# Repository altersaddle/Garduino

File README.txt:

The purpose of this project is to enable data collection and eventually action to keep
plants alive in a garden.

This project encompasses five components:

1) The "Garduino" device itself, which manages the sensors and external controls

2) The Arduino software that's running on the device

3) A serial monitor that accepts serial (via bluetooth) data from the Garduino

4) A database to keep all of the data

5) A reporting application / system to let users manage the data

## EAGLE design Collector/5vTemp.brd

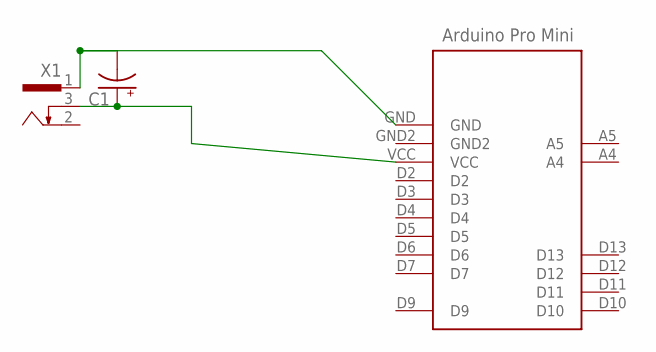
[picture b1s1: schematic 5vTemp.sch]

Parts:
C1: CPOL-USSANYO_C; SANYO-OSCON_C
U$1: ARDUINO_PRO_MINI_5V_V2V2; ARDUINO_PRO_MINI_5V_V2
X1: 733980-62

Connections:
unnamed: C1.+, U$1.VCC, X1.3
unnamed: C1.-, U$1.GND, X1.1

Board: 2 copper layers, 3 parts (0 on the bottom side), 2 nets, no tracks yet.

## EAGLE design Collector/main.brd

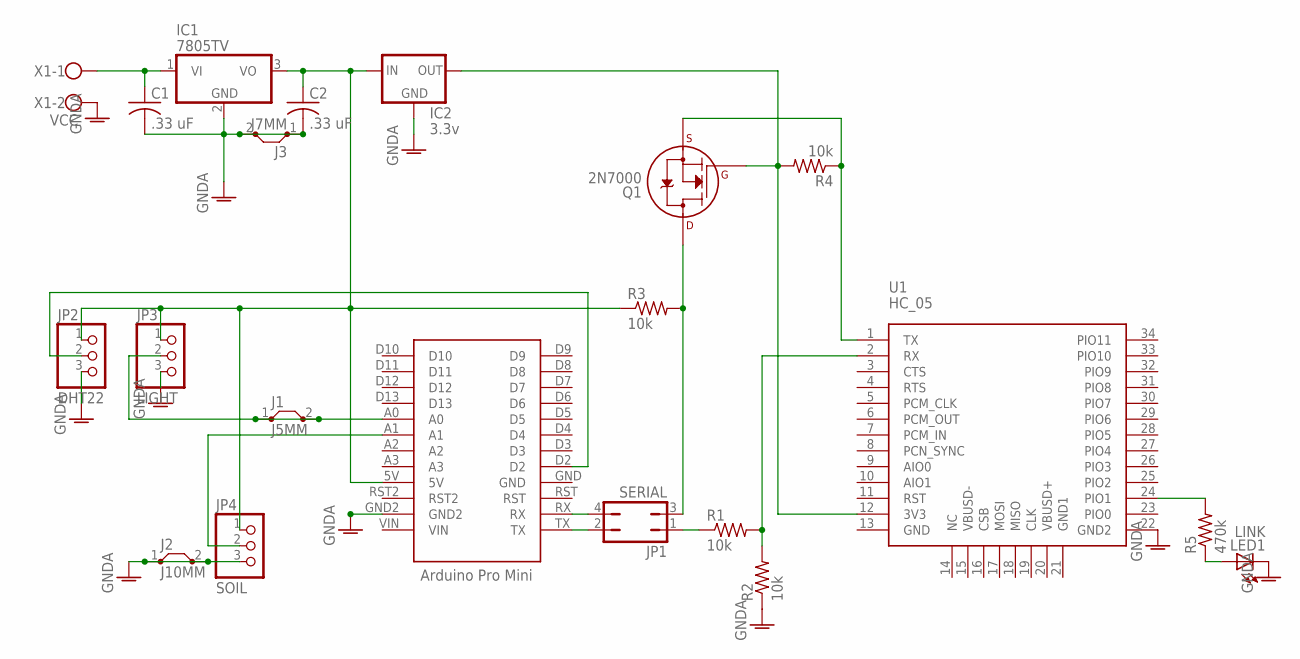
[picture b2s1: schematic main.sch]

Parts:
C1, C2: .33 uF; C025-050X050
IC1: 7805TV; TO220V
IC2: 3.3v; TO92-INLINE
J1: J5MM; 05
J2: J10MM; 10
J3: J7MM; 07
JP1: SERIAL; JP2Q
JP2: DHT22; 1X03
JP3: LIGHT; 1X03
JP4: SOIL; 1X03
LED1: LINK; LED3MM
Q1: 2N7000; TO-92
R1, R2, R3, R4: 10k; 0204/7
R5: 470k; 0204/7
U1: HC_05; BLUETOOTH_SMD
U$1: ARDUINO_PRO_MINI_5V_V1V1; ARDUINO_PRO_MINI_5V_V1
X1: VCC; W237-102

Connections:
GNDA: C1.2, C2.2, IC1.2 (GND), IC2.1 (GND), J2.1, J2.2, J3.1, J3.2, JP2.3, JP3.3, JP4.3, LED1.K (C), R2.1, U1.22 (GND2), U$1.GND2, X1.2
unnamed: IC2.3 (OUT), Q1.2 (G), R4.2, U1.12 (3V3)
unnamed: JP1.2, U$1.TX
unnamed: R1.2, R2.2, U1.2 (RX)
unnamed: C1.1, IC1.1 (VI), X1.1
unnamed: JP1.3, Q1.3 (D), R3.2
unnamed: Q1.1 (S), R4.1, U1.1 (TX)
unnamed: JP1.1, R1.1
unnamed: JP1.4, U$1.RX
unnamed: LED1.A, R5.1
unnamed: R5.2, U1.24 (PIO1)
unnamed: C2.1, IC1.3 (VO), IC2.2 (IN), JP2.1, JP3.1, JP4.1, R3.1, U$1.5V
unnamed: J1.1, J1.2, JP3.2, U$1.A0
unnamed: JP4.2, U$1.A1
unnamed: JP2.2, U$1.D2

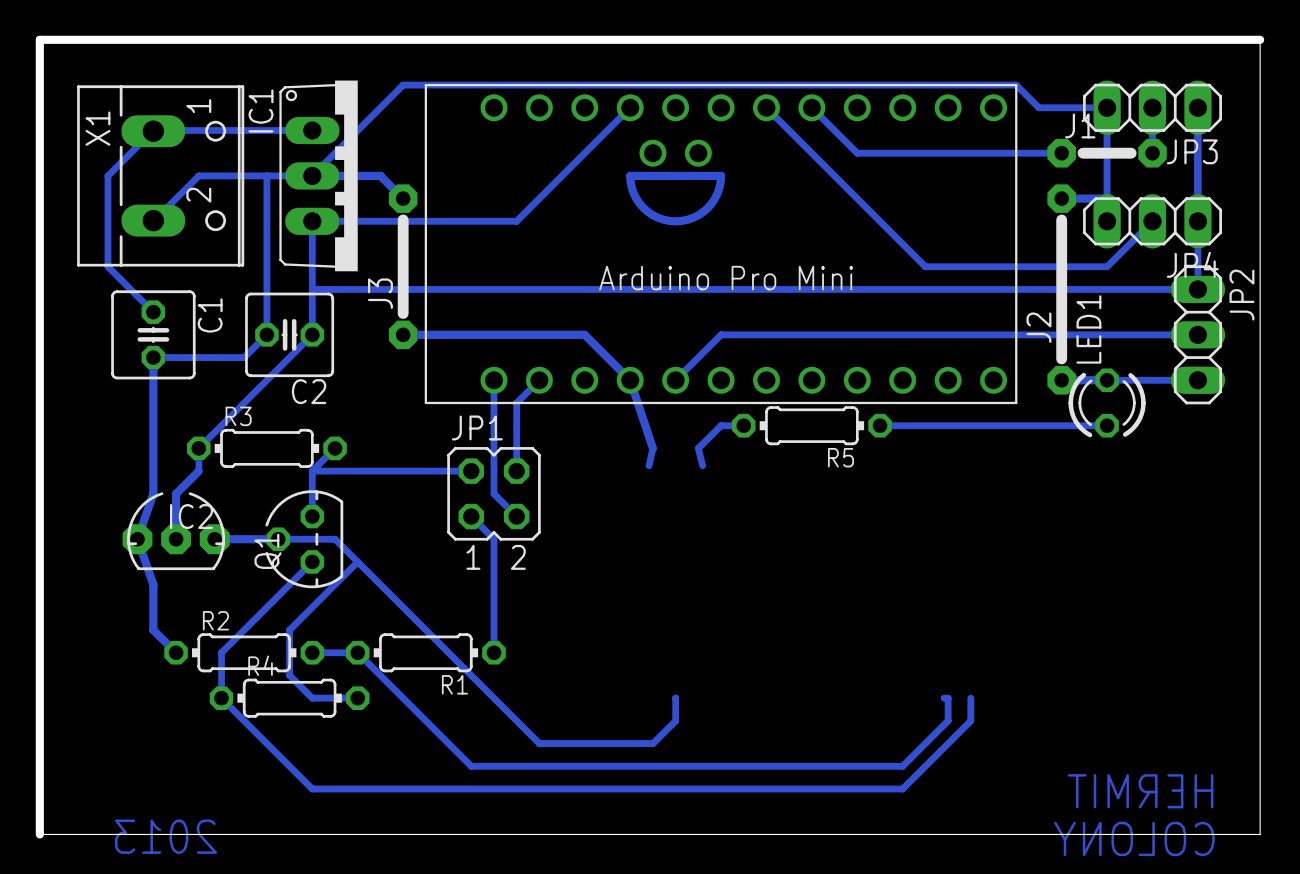
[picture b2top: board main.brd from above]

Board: 2 copper layers, 68.2 x 44.4 mm, 21 parts (1 on the bottom side), 15 nets.

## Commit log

2013-07-20 Initial import
    The files that we have so far.
2013-07-20 Added a readme
2013-07-20 READMEs for database and reporting
2013-07-20 Charting web site with no live data yet
2013-07-20 SQL to generate databases and tables
2013-07-20 Inserting into a database
2013-07-20 Workaround to remove the extra comma
2013-07-20 Apparently arduino needs the files this way
2013-07-21 command line program to fetch past 24hour average
2013-07-21 Output some JSON to console
2013-07-22 working sample data!
2013-07-26 More test data; removed login
2013-07-30 rename index to html
2013-07-30 output humidity as well
2013-08-02 Split Listener out into its own class
2013-08-03 Some typos, move gui update into event
2013-08-10 rename events to better reflect purpose
2013-08-10 add index to sensor table, reduce query times
2013-08-10 30 day averages!
2013-08-10 Line is capitalized
2013-08-11 fix formatting of dates
2013-08-11 Apply MAX/AVG/MIN as convention
2013-08-11 How about some CSS
2013-08-11 New bg color
2013-08-11 new bg color (attempt 2)
2013-08-11 add graph for light sensor
2013-11-04 Improve error handling, add variable for timing
2013-11-11 new variable names for consistency
2013-11-12 error handling in index page
2013-11-12 Adding div close tag seems to fix IE
2013-11-15 Arduino simulator app
2013-11-16 Updated simulator with two outputs
2013-11-16 Stub projects for expansion
2013-11-16 Debugging and callbacks
2013-12-10 Adding app.config files, stub service
2016-01-16 Store connection string external to application
2019-04-03 EAGLE files for Collector
    EAGLE files for 5v powered temp monitor
2019-04-03 Adding emoncms collector prototypes
